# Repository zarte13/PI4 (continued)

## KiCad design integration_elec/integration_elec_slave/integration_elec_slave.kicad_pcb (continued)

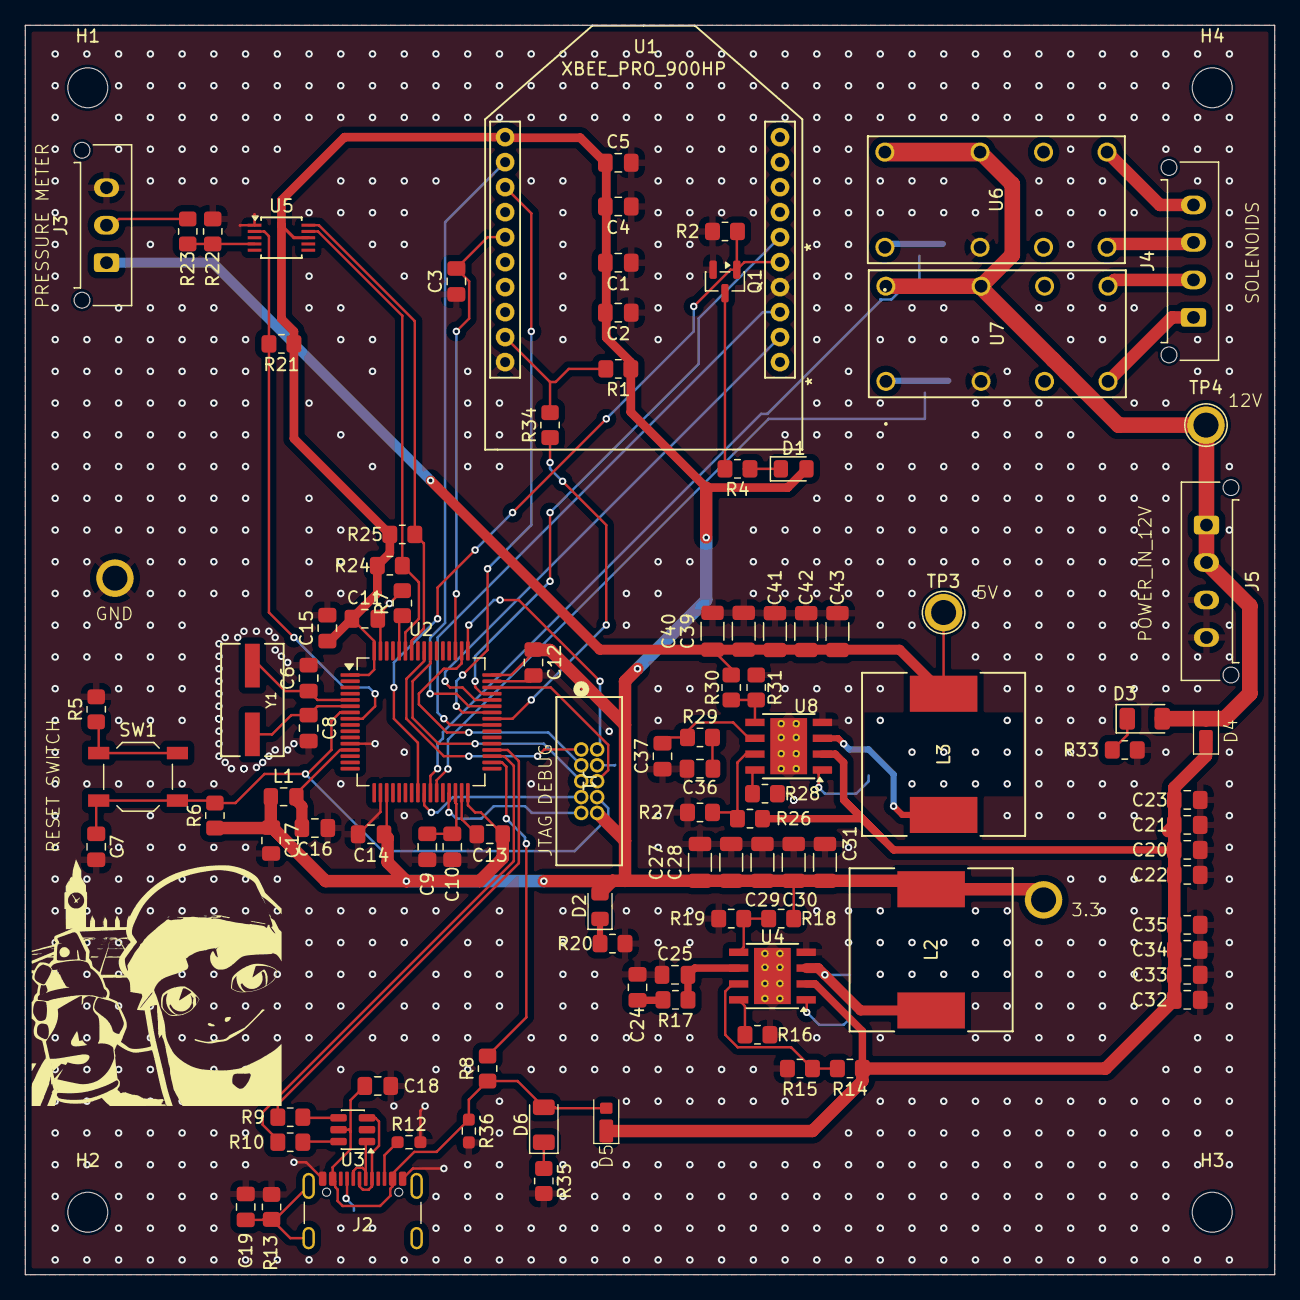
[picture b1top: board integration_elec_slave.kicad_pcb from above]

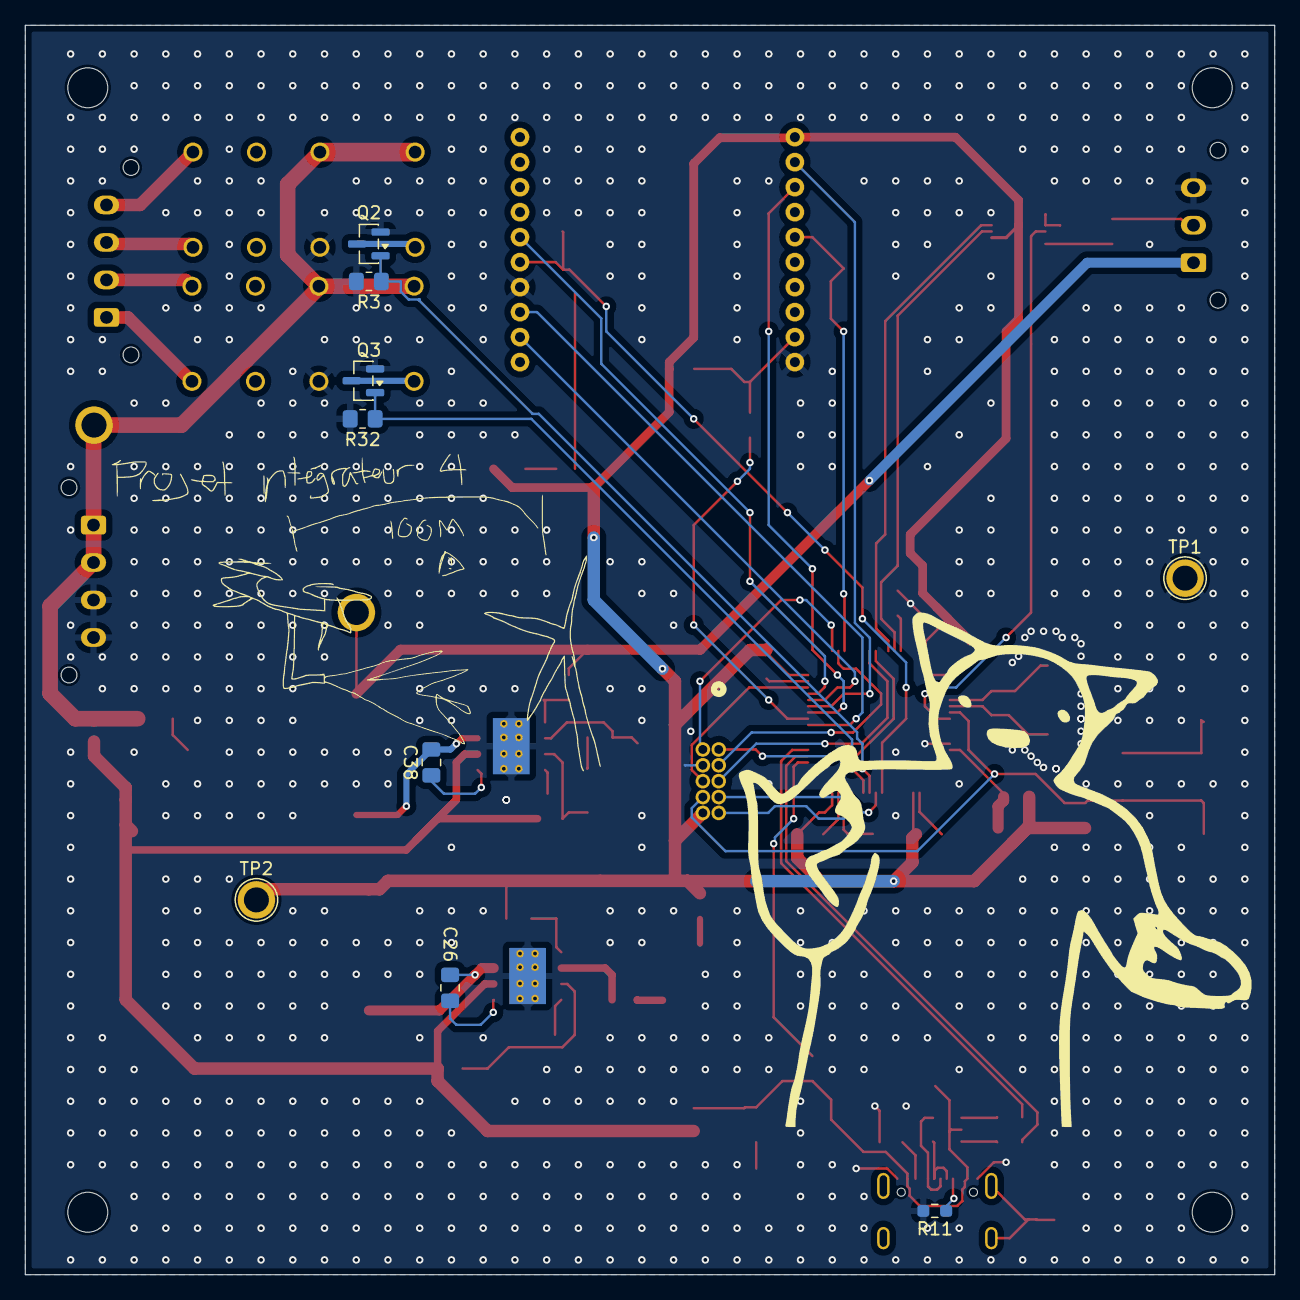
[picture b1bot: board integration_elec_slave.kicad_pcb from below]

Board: 2 copper layers, 100.0 x 100.0 mm, 114 parts (9 on the bottom side), 71 nets.

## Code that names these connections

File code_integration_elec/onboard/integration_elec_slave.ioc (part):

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Mcu.Name=STM32F446R(C-E)Tx
Mcu.Package=LQFP64
Mcu.UserName=STM32F446RETx
PA10.GPIOParameters=GPIO_Label
PA10.GPIO_Label=XBEE_UART_OUT
PA10.Mode=Asynchronous
PA10.Signal=USART1_RX
PA13.Mode=Serial_Wire
PA13.Signal=SYS_JTMS-SWDIO
PA14.Mode=Serial_Wire
PA14.Signal=SYS_JTCK-SWCLK
PA8.GPIOParameters=GPIO_PuPd,GPIO_Label
PA8.GPIO_Label=XBEE_RQ
PA8.GPIO_PuPd=GPIO_PULLDOWN
PA8.Signal=GPIO_Output
PA9.GPIOParameters=GPIO_Label
PA9.GPIO_Label=XBEE_UART_IN
PA9.Mode=Asynchronous
PA9.Signal=USART1_TX
PB0.GPIOParameters=PinState,GPIO_Label
PB0.GPIO_Label=SOLENOID_1
PB0.PinState=GPIO_PIN_RESET
PB0.Signal=GPIO_Output
PB1.GPIOParameters=GPIO_Label
PB1.GPIO_Label=SOLENOID_2
PB1.Signal=GPIO_Output
PB13.Mode=Activate_VBUS_FS
PB13.Signal=USB_OTG_HS_VBUS
PB14.Mode=Device_Only_FS
PB14.Signal=USB_OTG_HS_DM
PB15.Mode=Device_Only_FS
PB15.Signal=USB_OTG_HS_DP
PB6.Mode=I2C
PB6.Signal=I2C1_SCL
PB7.Mode=I2C
PB7.Signal=I2C1_SDA
PC0.GPIOParameters=GPIO_PuPd,GPIO_Label,GPIO_ModeDefaultEXTI
PC0.GPIO_Label=INTERRUPT_ADC
PC0.GPIO_ModeDefaultEXTI=GPIO_MODE_IT_FALLING
PC0.GPIO_PuPd=GPIO_PULLUP
PC0.Signal=GPXTI0
PC10.GPIOParameters=GPIO_PuPd,GPIO_Label
PC10.GPIO_Label=XBEE_N_RESET
PC10.GPIO_PuPd=GPIO_PULLUP
PC10.Signal=GPIO_Output
PC4.GPIOParameters=GPIO_Label
PC4.GPIO_Label=XBEE_LED
PC4.Signal=GPIO_Input
PC9.GPIOParameters=GPIO_Label
PC9.GPIO_Label=XBEE_STATUS
PC9.Signal=GPIO_Input
PH0-OSC_IN.Mode=HSE-External-Oscillator
PH0-OSC_IN.Signal=RCC_OSC_IN
PH1-OSC_OUT.Mode=HSE-External-Oscillator
PH1-OSC_OUT.Signal=RCC_OSC_OUT
RCC.HSE_VALUE=16000000
RCC.SYSCLKFreq_VALUE=96000000
RCC.SYSCLKSource=RCC_SYSCLKSOURCE_PLLCLK
board=custom

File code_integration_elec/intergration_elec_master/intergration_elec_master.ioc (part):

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Mcu.Name=STM32F446R(C-E)Tx
Mcu.Package=LQFP64
Mcu.UserName=STM32F446RETx
PA10.Mode=Asynchronous
PA10.Signal=USART1_RX
PA11.Mode=CTS_RTS
PA11.Signal=USART1_CTS
PA12.Mode=CTS_RTS
PA12.Signal=USART1_RTS
PA13.Mode=Serial_Wire
PA13.Signal=SYS_JTMS-SWDIO
PA14.Mode=Serial_Wire
PA14.Signal=SYS_JTCK-SWCLK
PA2.GPIOParameters=GPIO_Label
PA2.GPIO_Label=Void_Display_Reset
PA2.Signal=GPIO_Output
PA3.GPIOParameters=GPIO_Label
PA3.GPIO_Label=TFT_DC
PA3.Signal=GPIO_Output
PA4.GPIOParameters=GPIO_Label
PA4.GPIO_Label=TFT_CS
PA4.Signal=GPIO_Output
PA5.Mode=Full_Duplex_Master
PA5.Signal=SPI1_SCK
PA6.Mode=Full_Duplex_Master
PA6.Signal=SPI1_MISO
PA7.Mode=Full_Duplex_Master
PA7.Signal=SPI1_MOSI
PA8.GPIOParameters=GPIO_Label
PA8.GPIO_Label=XBEE_RQ
PA8.Signal=GPIO_Output
PA9.Mode=Asynchronous
PA9.Signal=USART1_TX
PB13.GPIOParameters=GPIO_Label
PB13.GPIO_Label=USB_VBUS
PB13.Mode=Activate_VBUS_FS
PB13.Signal=USB_OTG_HS_VBUS
PB14.GPIOParameters=GPIO_Label
PB14.GPIO_Label=USB_D-
PB14.Mode=Device_Only_FS
PB14.Signal=USB_OTG_HS_DM
PB15.GPIOParameters=GPIO_Label
PB15.GPIO_Label=USB_D+
PB15.Mode=Device_Only_FS
PB15.Signal=USB_OTG_HS_DP
PC10.GPIOParameters=GPIO_Label
PC10.GPIO_Label=XBEE_nReset
PC10.Signal=GPIO_Output
PC4.GPIOParameters=GPIO_Label
PC4.GPIO_Label=XBEE_LED
PC4.Signal=GPIO_Output
PC7.GPIOParameters=GPIO_PuPd,GPIO_Label
PC7.GPIO_Label=VALVE_1
PC7.GPIO_PuPd=GPIO_PULLDOWN
PC7.Signal=GPIO_Input
PC8.GPIOParameters=GPIO_PuPd,GPIO_Label
PC8.GPIO_Label=VALVE_2
PC8.GPIO_PuPd=GPIO_PULLDOWN
PC8.Signal=GPIO_Input
PC9.GPIOParameters=GPIO_Label
PC9.GPIO_Label=XBEE_STATUS
PC9.Signal=GPIO_Input
PH0-OSC_IN.Mode=HSE-External-Oscillator
PH0-OSC_IN.Signal=RCC_OSC_IN
PH1-OSC_OUT.Mode=HSE-External-Oscillator
PH1-OSC_OUT.Signal=RCC_OSC_OUT
board=custom

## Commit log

2025-11-07 ajout des fichiers pour scripts matlab de simulation de tests laser + IR
2026-01-23 EM - Ajout master PCB
2026-01-23 EM - Ajout slave PCB
2026-01-23 EM - Ajout de readme pour les folders de footprint/symbols/3dparts
2026-01-23 jte touche
2026-01-23 EM - Ajout projets code
2026-01-27 EM - Ajout des schématiques XBEE, pas implémenté les footprints encore
2026-01-27 EM - Ajout des pages hiérarchiques pour le slave, next up : Master
2026-01-27 EM - Ajout des pages hiérarchiques pour le master, next : ajouter connecteurs pour les capteurs
2026-02-03 EM - Ajout des contraintes JLCPCB, passé à 4 couches
2026-02-03 EM - corrections last push
2026-02-05 Add footprint screen
2026-02-05 Added symbol for screen
2026-02-05 Added screen into schematic
2026-02-06 Added footprint, symbol, 3D model for joystick. Added schematic for Joystick and comments
2026-02-06 EM - Avancement du slave et determination ADC pour LTF6800
2026-02-06 Added switch in design + Footprint + symbol
2026-02-06 Added footprint
2026-02-06 EM - fuck it we merge et on cree deux branches
2026-02-08 EM - Création de la branche pour master avec un fichier pour commit mon changement
2026-02-08 Added plein de footprint
2026-02-08 Added comment for pull-down
2026-02-09 Layout started
2026-02-20 EM - Correction des bus
2026-02-20 EM - Fini schématique attente de review
2026-02-20 KAH - Fini schematic attente de review + correction BUS
2026-02-27 EM - Ajout John Pork et debut schematic
2026-02-27 EM - Fin du schématique, ajout de diode pour empêcher de backfeeder le USB. Début PCB et ajout carré 100x100
2026-02-28 EM - Avancement du placement du PCB, fini USB et RELAIS, en train de continuer micro et regulateurs
2026-02-28 EM - Ajout du copper zone et chaise musicale pour le micro et le USB
2026-02-28 EM - PCB pas mal terminé, on review ça soon
2026-02-28 EM - Attente de review, complété avec les 3D
2026-02-28 EM - Oublié de run le script de via-stitching
2026-03-01 KAH - layout continué, un imbecile a mis le 3v3 tout en bas a droite tres loin de tout
2026-03-02 KAH - finished layout + routing, waiting for review
2026-03-04 KAH - yipieeee
2026-03-04 EM - Review finale (final i guess)
2026-03-04 EM - Review pas mal finale
2026-03-08 KAH - added the part # for some pieces. MISSING R NC and USB-C conn
2026-03-10 EM - Clean-up avant de commencer le code
2026-03-14 last commit
2026-03-21 EM - Config du cubemx devrait être finie, début du code pour le ADS1015. Ajout de Todo. Next : finir ADS1015
2026-03-21 EM - Ajout du call back de l'interrupt de l'ADC, ajout de l'init de l'ADC qui sera à confirmer.
2026-03-21 EM - Ajout du callback DMA pour adc, à tester. Ajout du prototypage pour les xbee
2026-03-21 EM - continuation
2026-03-26 KAH - commencer le setup de MXCube, added files for the screen
2026-03-27 EM - Bin des affaires qui marchent (im losing it)
2026-03-27 EM - Ok j'ai fini pour ce matin (soir)
2026-03-27 KAH - ioc terminé, reste a fix la clock
2026-03-27 EM - USB fonctionne esti que c hot
2026-03-28 KAH - added screen and valve config NOT TESTED
2026-03-29 EM - Devrait pas mal être final
2026-03-30 EM - Ajout de l'état des valves, code envoyé a kassem
2026-04-04 EM - Version pas mal finale, testé et fonctionnel
2026-04-04 KAH - ajout d'un fichier PI4 Master avec la bonne version du code testé et fonctionnel (bcp de files sorry)
